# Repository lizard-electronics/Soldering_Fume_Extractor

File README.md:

# Soldering Fume Extractor
## [In Development...]
Portable soldering fume extractor based on an ATmega328P MCU.

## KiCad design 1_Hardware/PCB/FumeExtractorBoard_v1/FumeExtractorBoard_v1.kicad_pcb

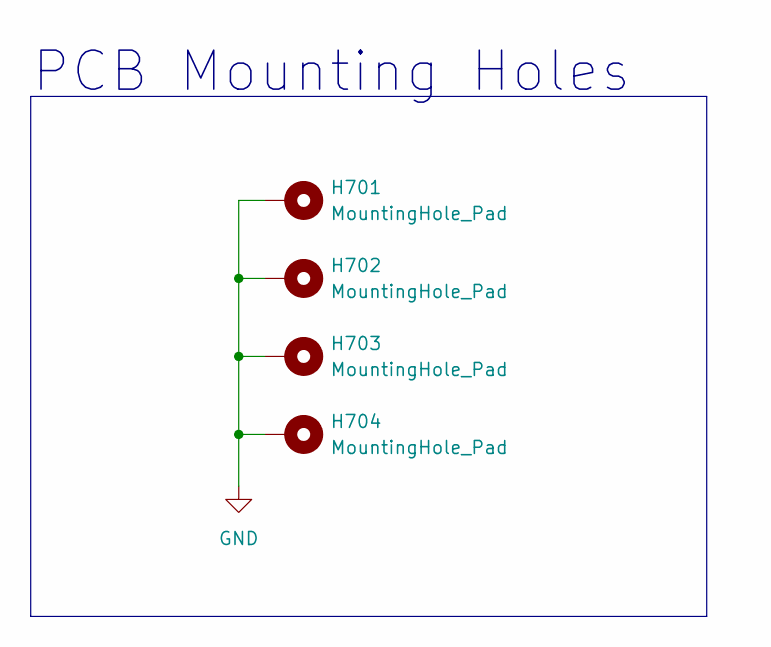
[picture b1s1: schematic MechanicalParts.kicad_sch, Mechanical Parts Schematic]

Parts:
H701, H702, H703, H704: MountingHole_Pad; MountingHole_3.2mm_M3_Pad_Via

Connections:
GND: H701.1, H702.1, H703.1, H704.1; also elsewhere on the board

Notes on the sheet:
PCB Mounting Holes

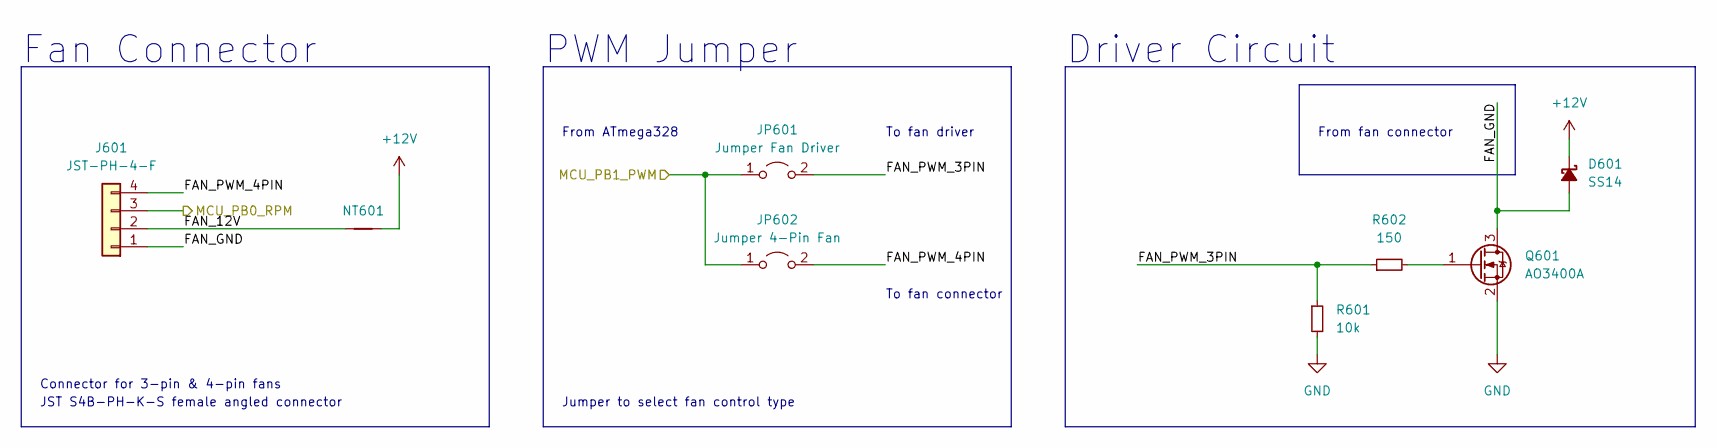
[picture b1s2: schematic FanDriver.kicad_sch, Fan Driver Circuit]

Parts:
D601: SS14; D_SMA
J601: JST-PH-4-F; JST_PH_S4B-PH-K_1x04_P2.00mm_Horizontal
JP601: Jumper Fan Driver; SolderJumper-2_P1.3mm_Open_RoundedPad1.0x1.5mm
JP602: Jumper 4-Pin Fan; SolderJumper-2_P1.3mm_Open_RoundedPad1.0x1.5mm
NT601: NetTie_2; NetTie-2_SMD_Pad0.5mm
Q601: AO3400A; SOT-23
R601: 10k; R_0603_1608Metric_Pad0.98x0.95mm_HandSolder
R602: 150; R_0805_2012Metric_Pad1.20x1.40mm_HandSolder

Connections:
+12V: D601.1 (K), NT601.2; also elsewhere on the board
/FanDriver/FAN_12V: J601.2, NT601.1
/FanDriver/FAN_GND: D601.2 (A), J601.1, Q601.3 (D)
/FanDriver/FAN_PWM_3PIN: JP601.2 (B), R601.1, R602.1
/FanDriver/FAN_PWM_4PIN: J601.4, JP602.2 (B)
/FanDriver/MCU_PB0_RPM: J601.3; also elsewhere on the board
/FanDriver/MCU_PB1_PWM: JP601.1 (A), JP602.1 (A); also elsewhere on the board
GND: Q601.2 (S), R601.2; also elsewhere on the board
unnamed: Q601.1 (G), R602.2

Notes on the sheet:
To fan connector
To fan driver
From fan connector
JST S4B-PH-K-S female angled connector
Fan Connector
PWM Jumper
Driver Circuit
Connector for 3-pin & 4-pin fans
From ATmega328
Jumper to select fan control type

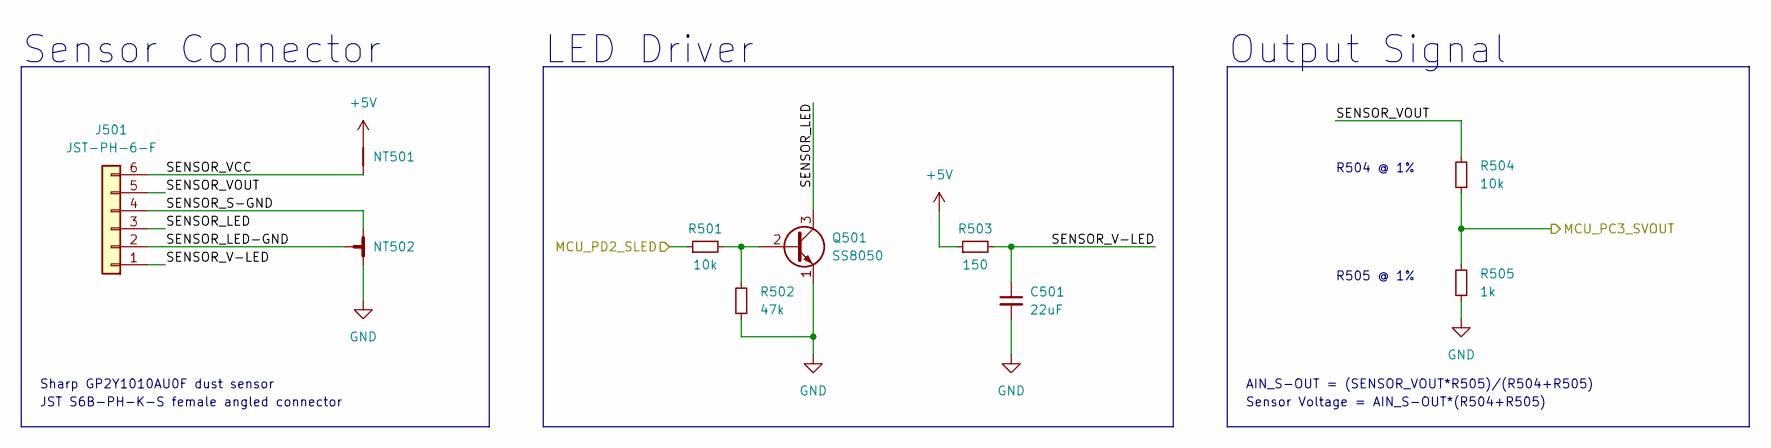
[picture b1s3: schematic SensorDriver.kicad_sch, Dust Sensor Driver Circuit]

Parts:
C501: 22uF; C_0805_2012Metric_Pad1.18x1.45mm_HandSolder
J501: JST-PH-6-F; JST_PH_S6B-PH-K_1x06_P2.00mm_Horizontal
NT501: NetTie_2; NetTie-2_SMD_Pad0.5mm
NT502: NetTie_3_Tee; NetTie-3_SMD_Pad0.5mm
Q501: SS8050; SOT-23
R501, R504: 10k; R_0603_1608Metric_Pad0.98x0.95mm_HandSolder
R502: 47k; R_0603_1608Metric_Pad0.98x0.95mm_HandSolder
R503: 150; R_0805_2012Metric_Pad1.20x1.40mm_HandSolder
R505: 1k; R_0603_1608Metric_Pad0.98x0.95mm_HandSolder

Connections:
+5V: NT501.2, R503.1; also elsewhere on the board
/MCU/MCU_PC3_SVOUT: R504.1, R505.2; also elsewhere on the board
/MCU/MCU_PD2_SLED: R501.1; also elsewhere on the board
/SensorDriver/SENSOR_LED: J501.3, Q501.3 (C)
/SensorDriver/SENSOR_LED-GND: J501.2, NT502.3
/SensorDriver/SENSOR_S-GND: J501.4, NT502.1
/SensorDriver/SENSOR_V-LED: C501.1, J501.1, R503.2
/SensorDriver/SENSOR_VCC: J501.6, NT501.1
/SensorDriver/SENSOR_VOUT: J501.5, R504.2
GND: C501.2, NT502.2, Q501.1 (E), R502.1, R505.1; also elsewhere on the board
unnamed: Q501.2 (B), R501.2, R502.2

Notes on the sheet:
R505 @ 1%
AIN_S-OUT = (SENSOR_VOUT*R505)/(R504+R505)
Sharp GP2Y1010AU0F dust sensor
Sensor Connector
Output Signal
Sensor Voltage = AIN_S-OUT*(R504+R505)
LED Driver
R504 @ 1%
JST S6B-PH-K-S female angled connector

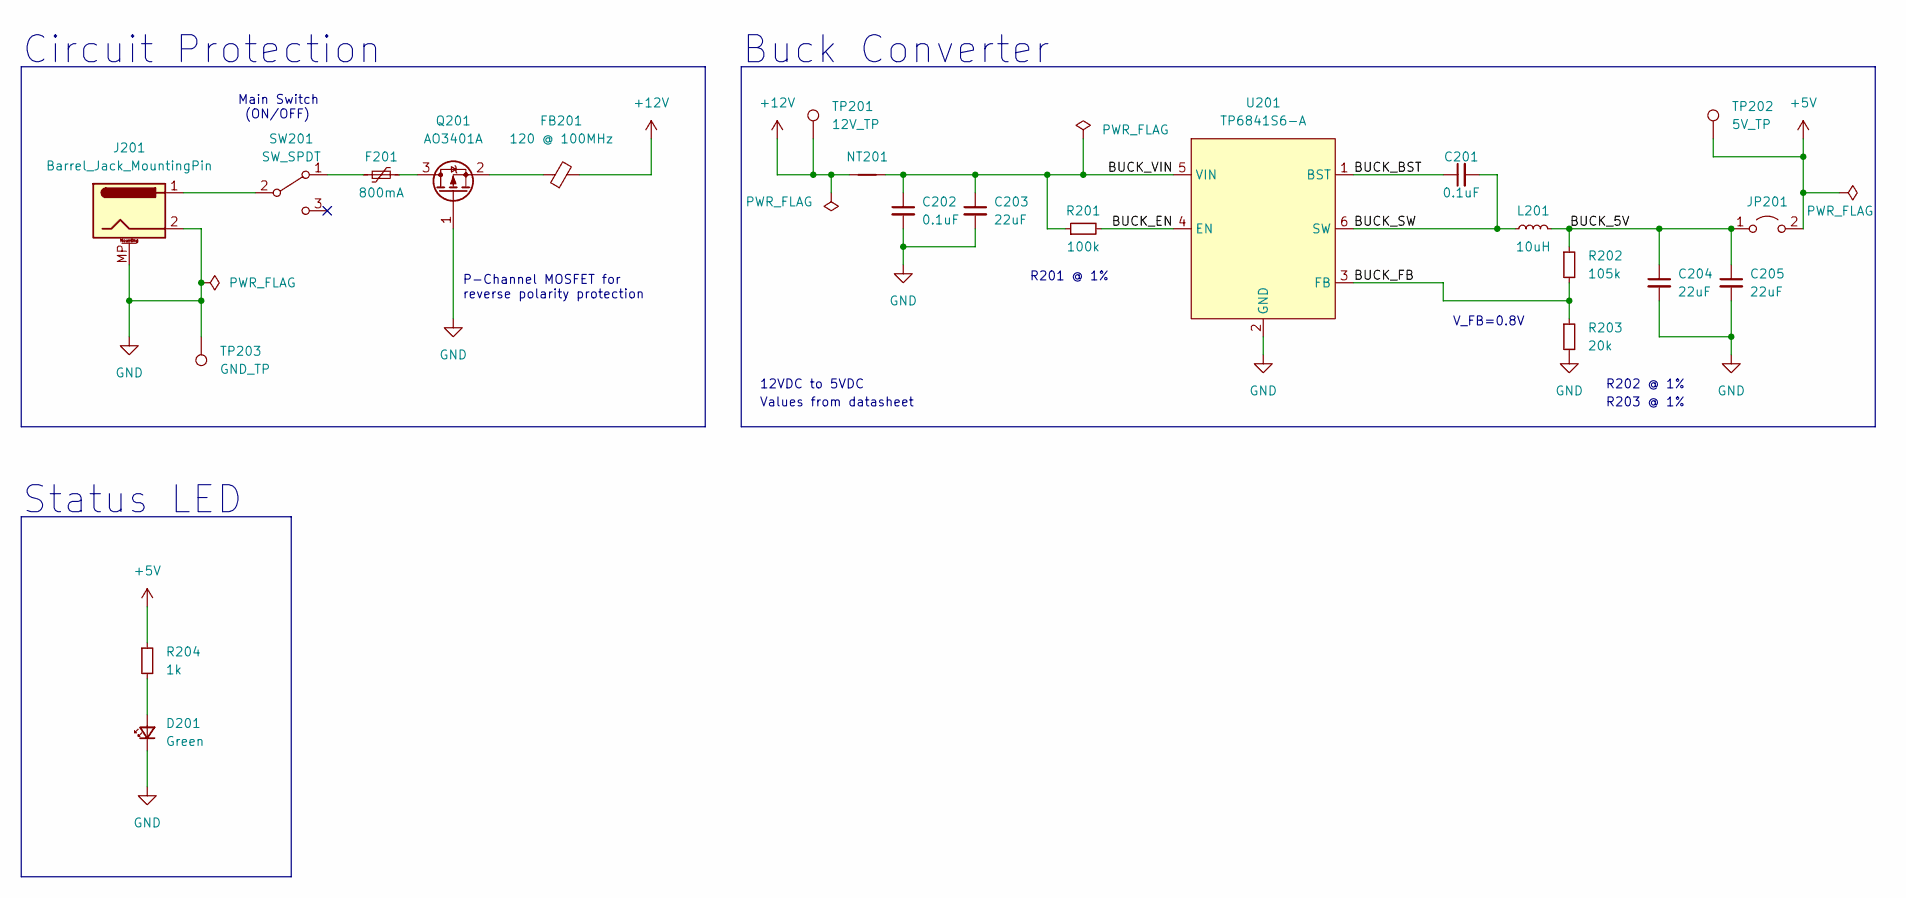
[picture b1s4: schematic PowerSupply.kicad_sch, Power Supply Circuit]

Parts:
C201: 0.1uF; C_0603_1608Metric_Pad1.08x0.95mm_HandSolder
C202: 0.1uF; C_0805_2012Metric_Pad1.18x1.45mm_HandSolder
C203, C204, C205: 22uF; C_0805_2012Metric_Pad1.18x1.45mm_HandSolder
D201: Green; LED_0805_2012Metric_Pad1.15x1.40mm_HandSolder
F201: 800mA; Fuse_1812_4532Metric
FB201: 120 @ 100MHz; L_0805_2012Metric_Pad1.05x1.20mm_HandSolder
J201: Barrel_Jack_MountingPin; BarrelJack_GCT_DCJ200-10-A_Horizontal
JP201: Jumper 5V; PinHeader_1x02_P2.54mm_Vertical
L201: 10uH; L_Sunlord_MWSA0518_5.4x5.2mm
NT201: NetTie_2; NetTie-2_SMD_Pad0.5mm
Q201: AO3401A; SOT-23
R201: 100k; R_0805_2012Metric_Pad1.20x1.40mm_HandSolder
R202: 105k; R_0805_2012Metric_Pad1.20x1.40mm_HandSolder
R203: 20k; R_0805_2012Metric_Pad1.20x1.40mm_HandSolder
R204: 1k; R_0805_2012Metric_Pad1.20x1.40mm_HandSolder
SW201: SW_SPDT; SW_Slide_1P2T_CK_OS102011MS2Q
TP201: 12V_TP; TestPoint_Pad_D1.5mm
TP202: 5V_TP; TestPoint_Pad_D1.5mm
TP203: GND_TP; TestPoint_Pad_D1.5mm
U201: TP6841S6-A; SOT-23-6

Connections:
+5V: JP201.2 (B), R204.1, TP202.1; also elsewhere on the board
+12V: FB201.2, NT201.1, TP201.1; also elsewhere on the board
/PowerSupply/BUCK_5V: C204.1, C205.1, JP201.1 (A), L201.2, R202.1
/PowerSupply/BUCK_BST: C201.1, U201.1 (BST)
/PowerSupply/BUCK_EN: R201.2, U201.4 (EN)
/PowerSupply/BUCK_FB: R202.2, R203.1, U201.3 (FB)
/PowerSupply/BUCK_SW: C201.2, L201.1, U201.6 (SW)
/PowerSupply/BUCK_VIN: C202.1, C203.1, NT201.2, R201.1, U201.5 (VIN)
GND: C202.2, C203.2, C204.2, C205.2, D201.1 (K), J201.2, J201.3, J201.MP (MountPin), Q201.1 (G), R203.2, TP203.1, U201.2 (GND); also elsewhere on the board
unnamed: D201.2 (A), R204.2
unnamed: F201.1, SW201.1 (A)
unnamed: F201.2, Q201.3 (D)
unnamed: FB201.1, Q201.2 (S)
unnamed: J201.1, SW201.2 (B)

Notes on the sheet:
R201 @ 1%
Circuit Protection
Buck Converter
Status LED
12VDC to 5VDC
R202 @ 1%
V_FB=0.8V
R203 @ 1%
Values from datasheet
P-Channel MOSFET for reverse polarity protection
Main Switch (ON/OFF)

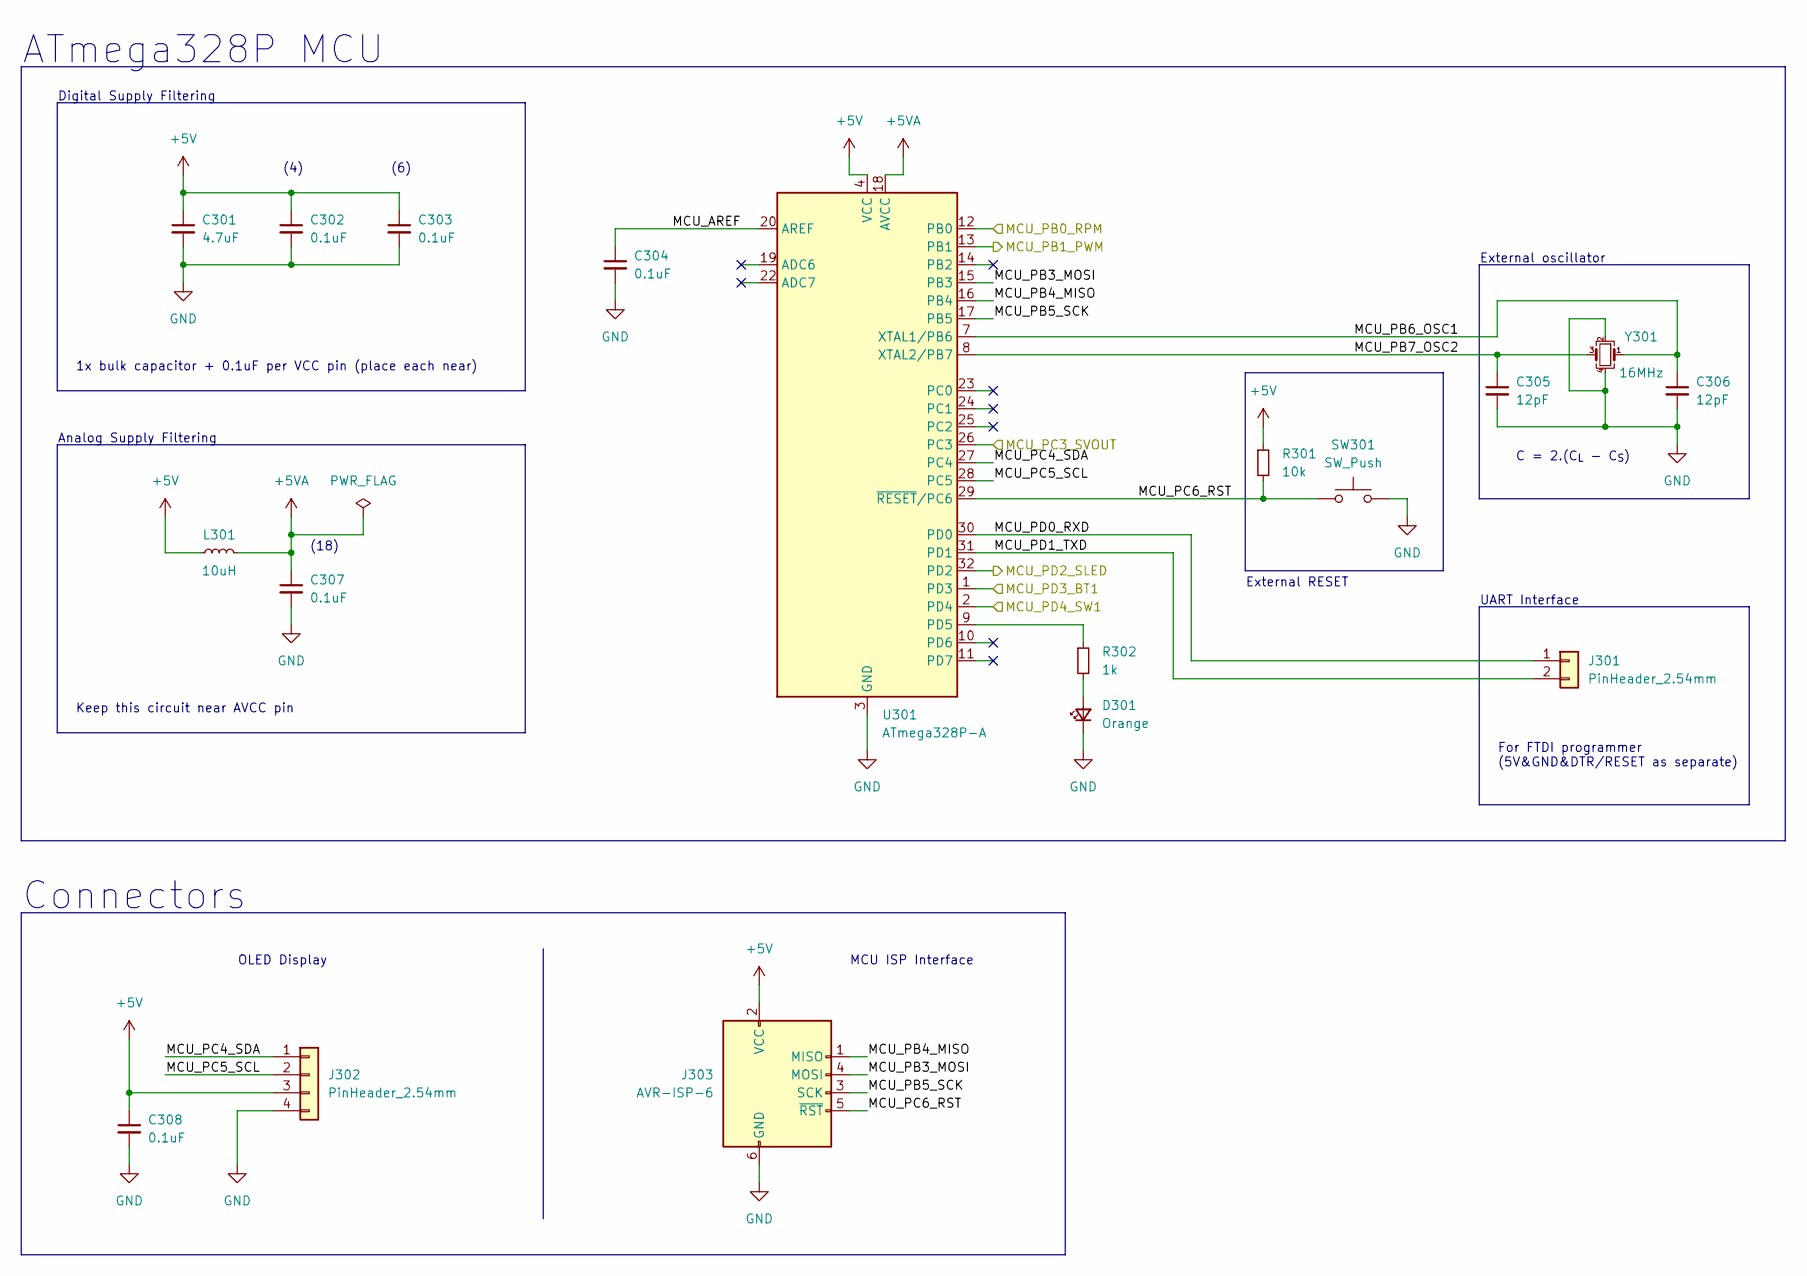
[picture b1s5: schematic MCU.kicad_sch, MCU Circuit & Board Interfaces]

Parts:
C301: 4.7uF; C_0805_2012Metric_Pad1.18x1.45mm_HandSolder
C302, C303, C304, C307, C308: 0.1uF; C_0603_1608Metric_Pad1.08x0.95mm_HandSolder
C305, C306: 12pF; C_0603_1608Metric_Pad1.08x0.95mm_HandSolder
D301: Orange; LED_0805_2012Metric_Pad1.15x1.40mm_HandSolder
J301: PinHeader_2.54mm; PinHeader_1x02_P2.54mm_Vertical
J302: PinHeader_2.54mm; PinSocket_1x04_P2.54mm_Vertical
J303: AVR-ISP-6; PinHeader_2x03_P2.54mm_Vertical
L301: 10uH; L_0805_2012Metric_Pad1.05x1.20mm_HandSolder
R301: 10k; R_0603_1608Metric_Pad0.98x0.95mm_HandSolder
R302: 1k; R_0805_2012Metric_Pad1.20x1.40mm_HandSolder
SW301: SW_Push; SW_SPST_TL3342
U301: ATmega328P-A; TQFP-32_7x7mm_P0.8mm
Y301: 16MHz; Crystal_SMD_3225-4Pin_3.2x2.5mm_HandSoldering

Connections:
+5V: C301.1, C302.1, C303.1, C308.1, J302.3, J303.2 (VCC), L301.1, R301.1, U301.4 (VCC), U301.6 (VCC); also elsewhere on the board
+5VA: C307.1, L301.2, U301.18 (AVCC)
/FanDriver/MCU_PB0_RPM: U301.12 (PB0); also elsewhere on the board
/FanDriver/MCU_PB1_PWM: U301.13 (PB1); also elsewhere on the board
/Inputs/MCU_PD3_BT1: U301.1 (PD3); also elsewhere on the board
/Inputs/MCU_PD4_SW1: U301.2 (PD4); also elsewhere on the board
/MCU/MCU_AREF: C304.1, U301.20 (AREF)
/MCU/MCU_PB3_MOSI: J303.4 (MOSI), U301.15 (PB3)
/MCU/MCU_PB4_MISO: J303.1 (MISO), U301.16 (PB4)
/MCU/MCU_PB5_SCK: J303.3 (SCK), U301.17 (PB5)
/MCU/MCU_PB6_OSC1: C306.1, U301.7 (XTAL1/PB6), Y301.1
/MCU/MCU_PB7_OSC2: C305.1, U301.8 (XTAL2/PB7), Y301.3
/MCU/MCU_PC3_SVOUT: U301.26 (PC3); also elsewhere on the board
/MCU/MCU_PC4_SDA: J302.1, U301.27 (PC4)
/MCU/MCU_PC5_SCL: J302.2, U301.28 (PC5)
/MCU/MCU_PC6_RST: J303.5 (~RST), R301.2, SW301.1, U301.29 (~RESET/PC6)
/MCU/MCU_PD0_RXD: J301.1, U301.30 (PD0)
/MCU/MCU_PD1_TXD: J301.2, U301.31 (PD1)
/MCU/MCU_PD2_SLED: U301.32 (PD2); also elsewhere on the board
GND: C301.2, C302.2, C303.2, C304.2, C305.2, C306.2, C307.2, C308.2, D301.1 (K), J302.4, J303.6 (GND), SW301.2, U301.3 (GND), U301.5 (GND), U301.21 (GND), Y301.2, Y301.4; also elsewhere on the board
unnamed: D301.2 (A), R302.2
unnamed: R302.1, U301.9 (PD5)

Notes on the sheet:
ATmega328P MCU
(4)
MCU ISP Interface
UART Interface
(18)
(6)
1x bulk capacitor + 0.1uF per VCC pin (place each near)
External RESET
Connectors
External oscillator
OLED Display
Digital Supply Filtering
C = 2.(C_{L} - C_{S})
Keep this circuit near AVCC pin
Analog Supply Filtering
For FTDI programmer (5V&GND&DTR/RESET as separate)

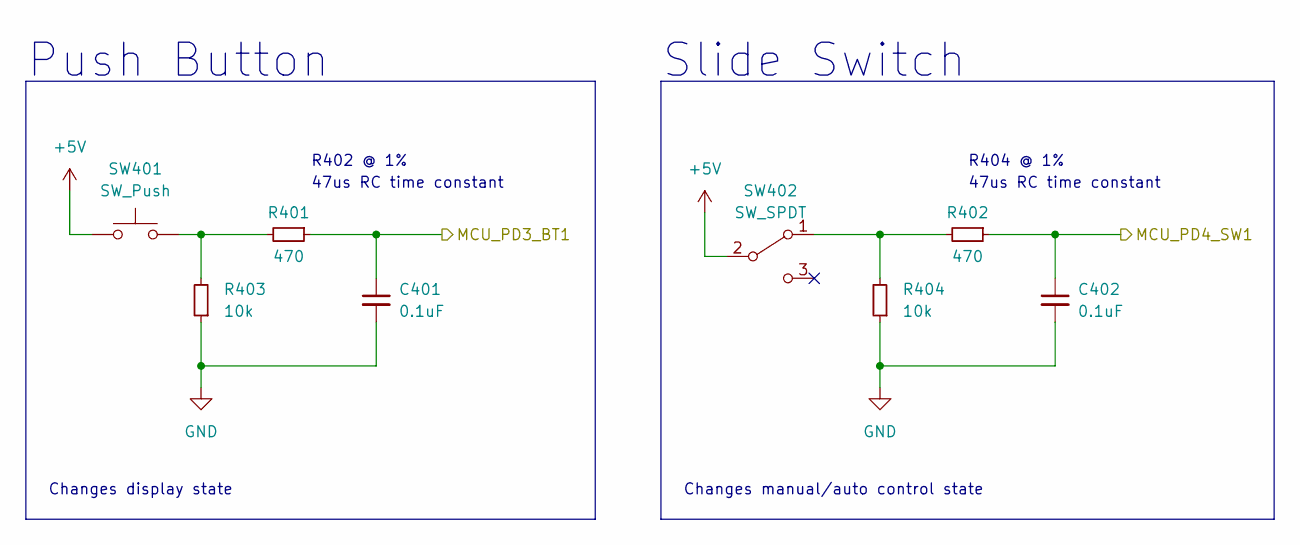
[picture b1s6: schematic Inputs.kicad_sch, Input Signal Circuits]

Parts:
C401, C402: 0.1uF; C_0603_1608Metric_Pad1.08x0.95mm_HandSolder
R401, R402: 470; R_0603_1608Metric_Pad0.98x0.95mm_HandSolder
R403, R404: 10k; R_0603_1608Metric_Pad0.98x0.95mm_HandSolder
SW401: SW_Push; SW_PUSH-12mm
SW402: SW_SPDT; SW_Slide_1P2T_CK_OS102011MS2Q

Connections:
+5V: SW401.1, SW402.2 (B); also elsewhere on the board
/Inputs/MCU_PD3_BT1: C401.1, R401.1; also elsewhere on the board
/Inputs/MCU_PD4_SW1: C402.1, R402.1; also elsewhere on the board
GND: C401.2, C402.2, R403.1, R404.1; also elsewhere on the board
unnamed: R401.2, R403.2, SW401.2
unnamed: R402.2, R404.2, SW402.1 (A)

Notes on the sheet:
R404 @ 1%
Slide Switch
Push Button
Changes display state
R402 @ 1%
Changes manual/auto control state
47us RC time constant

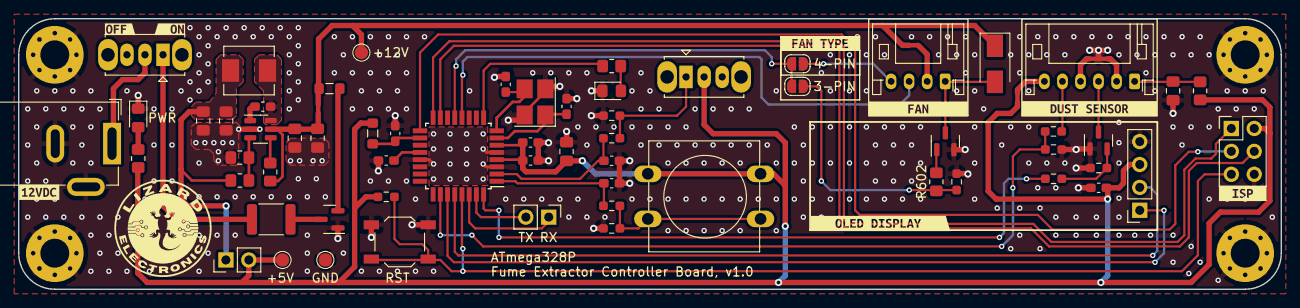
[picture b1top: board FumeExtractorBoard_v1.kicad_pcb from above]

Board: 2 copper layers, 140.0 x 30.0 mm, 79 parts (1 on the bottom side), 48 nets.

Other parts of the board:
kibuzzard-6334A8D3: G***; kibuzzard-6334A8D3
kibuzzard-63330C57: G***; kibuzzard-63330C57
kibuzzard-63330D54: G***; kibuzzard-63330D54
kibuzzard-63330DD6: G***; kibuzzard-63330DD6
kibuzzard-63330FE0: G***; kibuzzard-63330FE0
kibuzzard-633311A9: G***; kibuzzard-633311A9
kibuzzard-6333156D: G***; kibuzzard-6333156D
kibuzzard-63331390: G***; kibuzzard-63331390
kibuzzard-63331553: G***; kibuzzard-63331553

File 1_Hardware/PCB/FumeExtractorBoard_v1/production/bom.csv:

Designator,Footprint,Quantity,Value,LCSC Part #
"C201, C302, C303, C304, C307, C308, C401, C402",C_0603_1608Metric_Pad1.08x0.95mm_HandSolder,8,0.1uF,C14663
C202,C_0805_2012Metric_Pad1.18x1.45mm_HandSolder,1,0.1uF,C49678
"C203, C204, C205, C501",C_0805_2012Metric_Pad1.18x1.45mm_HandSolder,4,22uF,C45783
C301,C_0805_2012Metric_Pad1.18x1.45mm_HandSolder,1,4.7uF,C1779
"C305, C306",C_0603_1608Metric_Pad1.08x0.95mm_HandSolder,2,12pF,C1642
D201,LED_0805_2012Metric_Pad1.15x1.40mm_HandSolder,1,Green,C965815
D301,LED_0805_2012Metric_Pad1.15x1.40mm_HandSolder,1,Orange,C965813
D601,D_SMA,1,SS14,C2480
F201,Fuse_1812_4532Metric,1,800mA,C151168
FB201,L_0805_2012Metric_Pad1.05x1.20mm_HandSolder,1,120 @ 100MHz,C79382
"H701, H702, H703, H704",MountingHole_3.2mm_M3_Pad_Via,4,MountingHole_Pad,
J201,BarrelJack_GCT_DCJ200-10-A_Horizontal,1,Barrel_Jack_MountingPin,C718037
J301,PinHeader_1x02_P2.54mm_Vertical,1,PinHeader_2.54mm,
J302,PinHeader_1x04_P2.54mm_Vertical,1,PinHeader_2.54mm,
J303,PinHeader_2x03_P2.54mm_Vertical,1,AVR-ISP-6,C65114
J501,JST_PH_S6B-PH-K_1x06_P2.00mm_Horizontal,1,JST-PH-6-F,C157920
J601,JST_PH_S4B-PH-K_1x04_P2.00mm_Horizontal,1,JST-PH-4-F,C157926
JP201,PinHeader_1x02_P2.54mm_Vertical,1,Jumper 5V,
JP601,SolderJumper-2_P1.3mm_Open_RoundedPad1.0x1.5mm,1,Jumper Fan Driver,
JP602,SolderJumper-2_P1.3mm_Open_RoundedPad1.0x1.5mm,1,Jumper 4-Pin Fan,
L201,L_Sunlord_MWSA0518_5.4x5.2mm,1,10uH,C408349
L301,L_0805_2012Metric_Pad1.05x1.20mm_HandSolder,1,10uH,C99366
"NT201, NT501, NT601",NetTie-2_SMD_Pad0.5mm,3,NetTie_2,
NT502,NetTie-3_SMD_Pad0.5mm,1,NetTie_3_Tee,
Q201,SOT-23,1,AO3401A,C347476
Q501,SOT-23,1,SS8050,C2150
Q601,SOT-23,1,AO3400A,C700953
R201,R_0805_2012Metric_Pad1.20x1.40mm_HandSolder,1,100k,C149504
R202,R_0805_2012Metric_Pad1.20x1.40mm_HandSolder,1,105k,C2961513
R203,R_0805_2012Metric_Pad1.20x1.40mm_HandSolder,1,20k,C2907240
"R204, R302",R_0805_2012Metric_Pad1.20x1.40mm_HandSolder,2,1k,C2907232
"R301, R403, R404, R501, R504, R601",R_0603_1608Metric_Pad0.98x0.95mm_HandSolder,6,10k,C98220
"R401, R402",R_0603_1608Metric_Pad0.98x0.95mm_HandSolder,2,470,C2907041
R502,R_0603_1608Metric_Pad0.98x0.95mm_HandSolder,1,47k,C2907042
"R503, R602",R_0805_2012Metric_Pad1.20x1.40mm_HandSolder,2,150,C17471
R505,R_0603_1608Metric_Pad0.98x0.95mm_HandSolder,1,1k,C2907002
"SW201, SW402",SW_Slide_1P2T_CK_OS102011MS2Q,2,SW_SPDT,C2800116
SW301,SW_SPST_TL3342,1,SW_Push,C2886894
SW401,SW_PUSH-12mm,1,SW_Push,C455206
TP201,TestPoint_Pad_D1.5mm,1,12V_TP,
TP202,TestPoint_Pad_D1.5mm,1,5V_TP,
TP203,TestPoint_Pad_D1.5mm,1,GND_TP,
U201,SOT-23-6,1,TP6841S6-A,C2844924
U301,TQFP-32_7x7mm_P0.8mm,1,ATmega328P-A,C14877
Y301,Crystal_SMD_3225-4Pin_3.2x2.5mm_HandSoldering,1,16MHz,C112972

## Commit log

2023-02-27 File Organization
    1. Synchronization with GitHub repository.
    2. Added software files from developed test programs.
2023-02-27 File Organization
